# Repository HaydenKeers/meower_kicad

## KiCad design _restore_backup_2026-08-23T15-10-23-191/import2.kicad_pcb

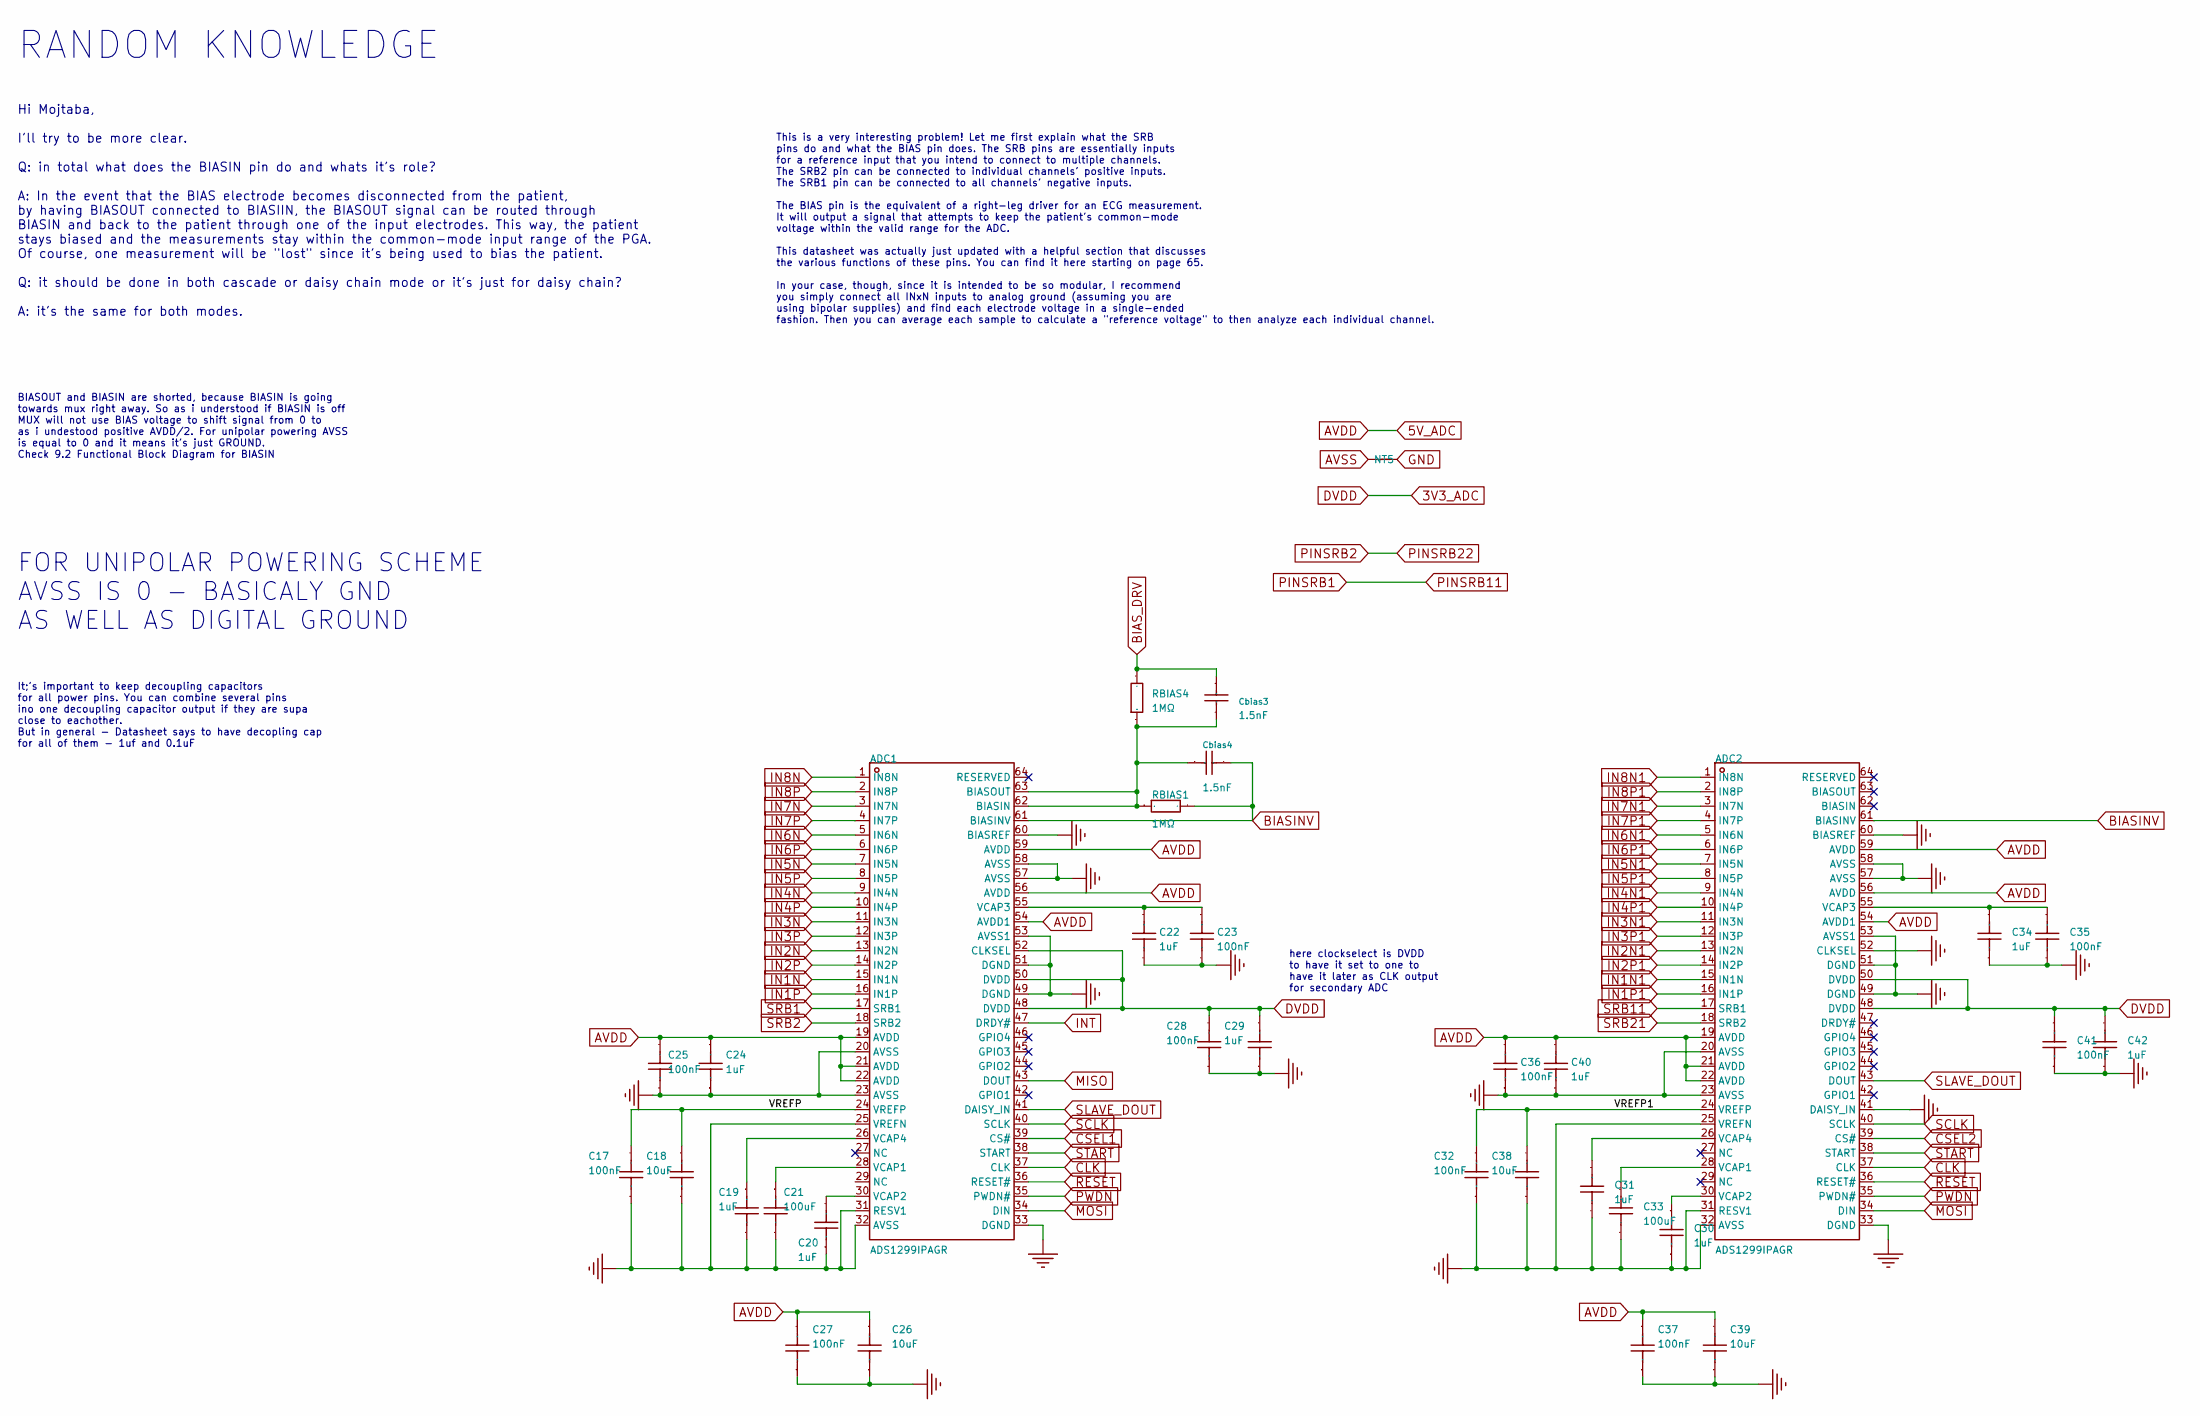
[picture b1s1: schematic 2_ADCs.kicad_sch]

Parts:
ADC1, ADC2: ADS1299IPAGR; TQFP-64_L10.0-W10.0-P0.50-LS12.0-TL; Voltage - Supply 4.75V~5.25V; Voltage Reference Drift 35ppm/℃; Manufacturer Part ADS1299IPAGR; LCSC Part Name ADS1299-x 低噪声、4/6/8通道、24bit 、同时采样模数转换器，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
C17, C23, C25, C27, C28, C32, C35, C36, C37, C41: 100nF; C0603; Manufacturer Part GRM188R71H104KA93D; LCSC Part Name 100nF ±10% 50V
C18, C26, C38, C39: 10uF; C0805; Manufacturer Part GRM188R61A106KE69D; LCSC Part Name 10uF ±10% 10V
C19, C20, C22, C30, C31, C34: 1uF; C0603; Manufacturer Part GRM188R61E105KA12D; LCSC Part Name 1uF ±10% 25V
C21, C33: 100uF; C1210; Manufacturer Part LMK325BJ107MM-T; LCSC Part Name 100uF ±20% 10V
C24, C29, C40, C42: 1uF; C0805; Manufacturer Part GRM188R61E105KA12D; LCSC Part Name 1uF ±10% 25V
Cbias3, Cbias4: 1.5nF; C0402; Voltage Rating 50V; Manufacturer Part GCM155R71H152KA37D; LCSC Part Name 1.5nF ±10% 50V
NT5: NetTie_2; NetTie-2_SMD_Pad0.5mm
RBIAS1, RBIAS4: 1MΩ; R0603; Manufacturer Part RC0402FR-071ML; LCSC Part Name 厚膜电阻 1MΩ ±1% 62.5mW

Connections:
3V3_ADC: ADC1.48 (DVDD), ADC1.50 (DVDD), ADC1.52 (CLKSEL), ADC2.48 (DVDD), ADC2.50 (DVDD), C28.2, C29.2, C41.2, C42.2; also elsewhere on the board
5V_ADC: ADC1.19 (AVDD), ADC1.21 (AVDD), ADC1.22 (AVDD), ADC1.54 (AVDD1), ADC1.56 (AVDD), ADC1.59 (AVDD), ADC2.19 (AVDD), ADC2.21 (AVDD), ADC2.22 (AVDD), ADC2.54 (AVDD1), ADC2.56 (AVDD), ADC2.59 (AVDD), C24.2, C25.2, C26.2, C27.2, C36.2, C37.2, C39.2, C40.2; also elsewhere on the board
/ADCs/VREFP: ADC1.24 (VREFP), C17.2, C18.2
/ADCs/VREFP1: ADC2.24 (VREFP), C32.2, C38.2
AVSS: ADC1.20 (AVSS), ADC1.23 (AVSS), ADC1.25 (VREFN), ADC1.31 (RESV1), ADC1.32 (AVSS), ADC1.57 (AVSS), ADC1.58 (AVSS), ADC1.60 (BIASREF), ADC2.20 (AVSS), ADC2.23 (AVSS), ADC2.25 (VREFN), ADC2.31 (RESV1), ADC2.32 (AVSS), ADC2.57 (AVSS), ADC2.58 (AVSS), ADC2.60 (BIASREF), C17.1, C18.1, C19.2, C20.1, C21.2, C24.1, C25.1, C30.1, C31.2, C32.1, C33.2, C36.1, C38.1, C40.1, NT5.1; also elsewhere on the board
BIASINV: ADC1.61 (BIASINV), ADC2.61 (BIASINV), Cbias4.2, RBIAS1.2
BIAS_DRV: Cbias3.1, RBIAS4.2; also elsewhere on the board
CLK: ADC1.37 (CLK), ADC2.37 (CLK)
CSEL1: ADC1.39 (CS#); also elsewhere on the board
CSEL2: ADC2.39 (CS#); also elsewhere on the board
GND: ADC1.33 (DGND), ADC1.49 (DGND), ADC1.51 (DGND), ADC1.53 (AVSS1), ADC2.33 (DGND), ADC2.41 (DAISY_IN), ADC2.49 (DGND), ADC2.51 (DGND), ADC2.52 (CLKSEL), ADC2.53 (AVSS1), C22.2, C23.2, C26.1, C27.1, C28.1, C29.1, C34.2, C35.2, C37.1, C39.1, C41.1, C42.1, NT5.2; also elsewhere on the board
IN1N: ADC1.15 (IN1N); also elsewhere on the board
IN1N1: ADC2.15 (IN1N); also elsewhere on the board
IN1P: ADC1.16 (IN1P); also elsewhere on the board
IN1P1: ADC2.16 (IN1P); also elsewhere on the board
IN2N: ADC1.13 (IN2N); also elsewhere on the board
IN2N1: ADC2.13 (IN2N); also elsewhere on the board
IN2P: ADC1.14 (IN2P); also elsewhere on the board
IN2P1: ADC2.14 (IN2P); also elsewhere on the board
IN3N: ADC1.11 (IN3N); also elsewhere on the board
IN3N1: ADC2.11 (IN3N); also elsewhere on the board
IN3P: ADC1.12 (IN3P); also elsewhere on the board
IN3P1: ADC2.12 (IN3P); also elsewhere on the board
IN4N: ADC1.9 (IN4N); also elsewhere on the board
IN4N1: ADC2.9 (IN4N); also elsewhere on the board
IN4P: ADC1.10 (IN4P); also elsewhere on the board
IN4P1: ADC2.10 (IN4P); also elsewhere on the board
IN5N: ADC1.7 (IN5N); also elsewhere on the board
IN5N1: ADC2.7 (IN5N); also elsewhere on the board
IN5P: ADC1.8 (IN5P); also elsewhere on the board
IN5P1: ADC2.8 (IN5P); also elsewhere on the board
IN6N: ADC1.5 (IN6N); also elsewhere on the board
IN6N1: ADC2.5 (IN6N); also elsewhere on the board
IN6P: ADC1.6 (IN6P); also elsewhere on the board
IN6P1: ADC2.6 (IN6P); also elsewhere on the board
IN7N: ADC1.3 (IN7N); also elsewhere on the board
IN7N1: ADC2.3 (IN7N); also elsewhere on the board
IN7P: ADC1.4 (IN7P); also elsewhere on the board
IN7P1: ADC2.4 (IN7P); also elsewhere on the board
IN8N: ADC1.1 (IN8N); also elsewhere on the board
IN8N1: ADC2.1 (IN8N); also elsewhere on the board
IN8P: ADC1.2 (IN8P); also elsewhere on the board
IN8P1: ADC2.2 (IN8P); also elsewhere on the board
INT: ADC1.47 (DRDY#); also elsewhere on the board
MISO: ADC1.43 (DOUT); also elsewhere on the board
MOSI: ADC1.34 (DIN), ADC2.34 (DIN); also elsewhere on the board
unnamed: ADC1.62 (BIASIN), ADC1.63 (BIASOUT), Cbias3.2, Cbias4.1, RBIAS1.1, RBIAS4.1
unnamed: ADC1.28 (VCAP1), C21.1
unnamed: ADC1.30 (VCAP2), C20.2
unnamed: ADC1.55 (VCAP3), C22.1, C23.1
unnamed: ADC1.26 (VCAP4), C19.1
unnamed: ADC2.28 (VCAP1), C33.1
unnamed: ADC2.30 (VCAP2), C30.2
unnamed: ADC2.55 (VCAP3), C34.1, C35.1
unnamed: ADC2.26 (VCAP4), C31.1
PWDN: ADC1.35 (PWDN#), ADC2.35 (PWDN#); also elsewhere on the board
RESET: ADC1.36 (RESET#), ADC2.36 (RESET#); also elsewhere on the board
SCLK: ADC1.40 (SCLK), ADC2.40 (SCLK); also elsewhere on the board
SLAVE_DOUT: ADC1.41 (DAISY_IN), ADC2.43 (DOUT)
SRB1: ADC1.17 (SRB1); also elsewhere on the board
SRB2: ADC1.18 (SRB2); also elsewhere on the board
SRB11: ADC2.17 (SRB1); also elsewhere on the board
SRB21: ADC2.18 (SRB2); also elsewhere on the board
START: ADC1.38 (START), ADC2.38 (START); also elsewhere on the board

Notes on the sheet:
It;'s important to keep decoupling capacitors for all power pins. You can combine several pins ino one decoupling capacitor output if they are supa close to eachother. But in general - Datasheet says to have decopling cap for all of them - 1uf and 0.1uF
FOR UNIPOLAR POWERING SCHEME AVSS IS 0 - BASICALY GND AS WELL AS DIGITAL GROUND
Hi Mojtaba, I'll try to be more clear. Q: in total what does the BIASIN pin do and whats it's role? A: In the event that the BIAS electrode becomes disconnected from the patient, by having BIASOUT connected to BIASIIN, the BIASOUT signal can be routed through BIASIN and back to the patient through 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
BIASOUT and BIASIN are shorted, because BIASIN is going towards mux right away. So as i understood if BIASIN is off MUX will not use BIAS voltage to shift signal from 0 to as i undestood positive AVDD/2. For unipolar powering AVSS is equal to 0 and it means it's just GROUND. Check 9.2 Functional Bl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
here clockselect is DVDD to have it set to one to have it later as CLK output for secondary ADC
This is a very interesting problem! Let me first explain what the SRB pins do and what the BIAS pin does. The SRB pins are essentially inputs for a reference input that you intend to connect to multiple channels. The SRB2 pin can be connected to individual channels' positive inputs. The SRB1 pin ca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
RANDOM KNOWLEDGE

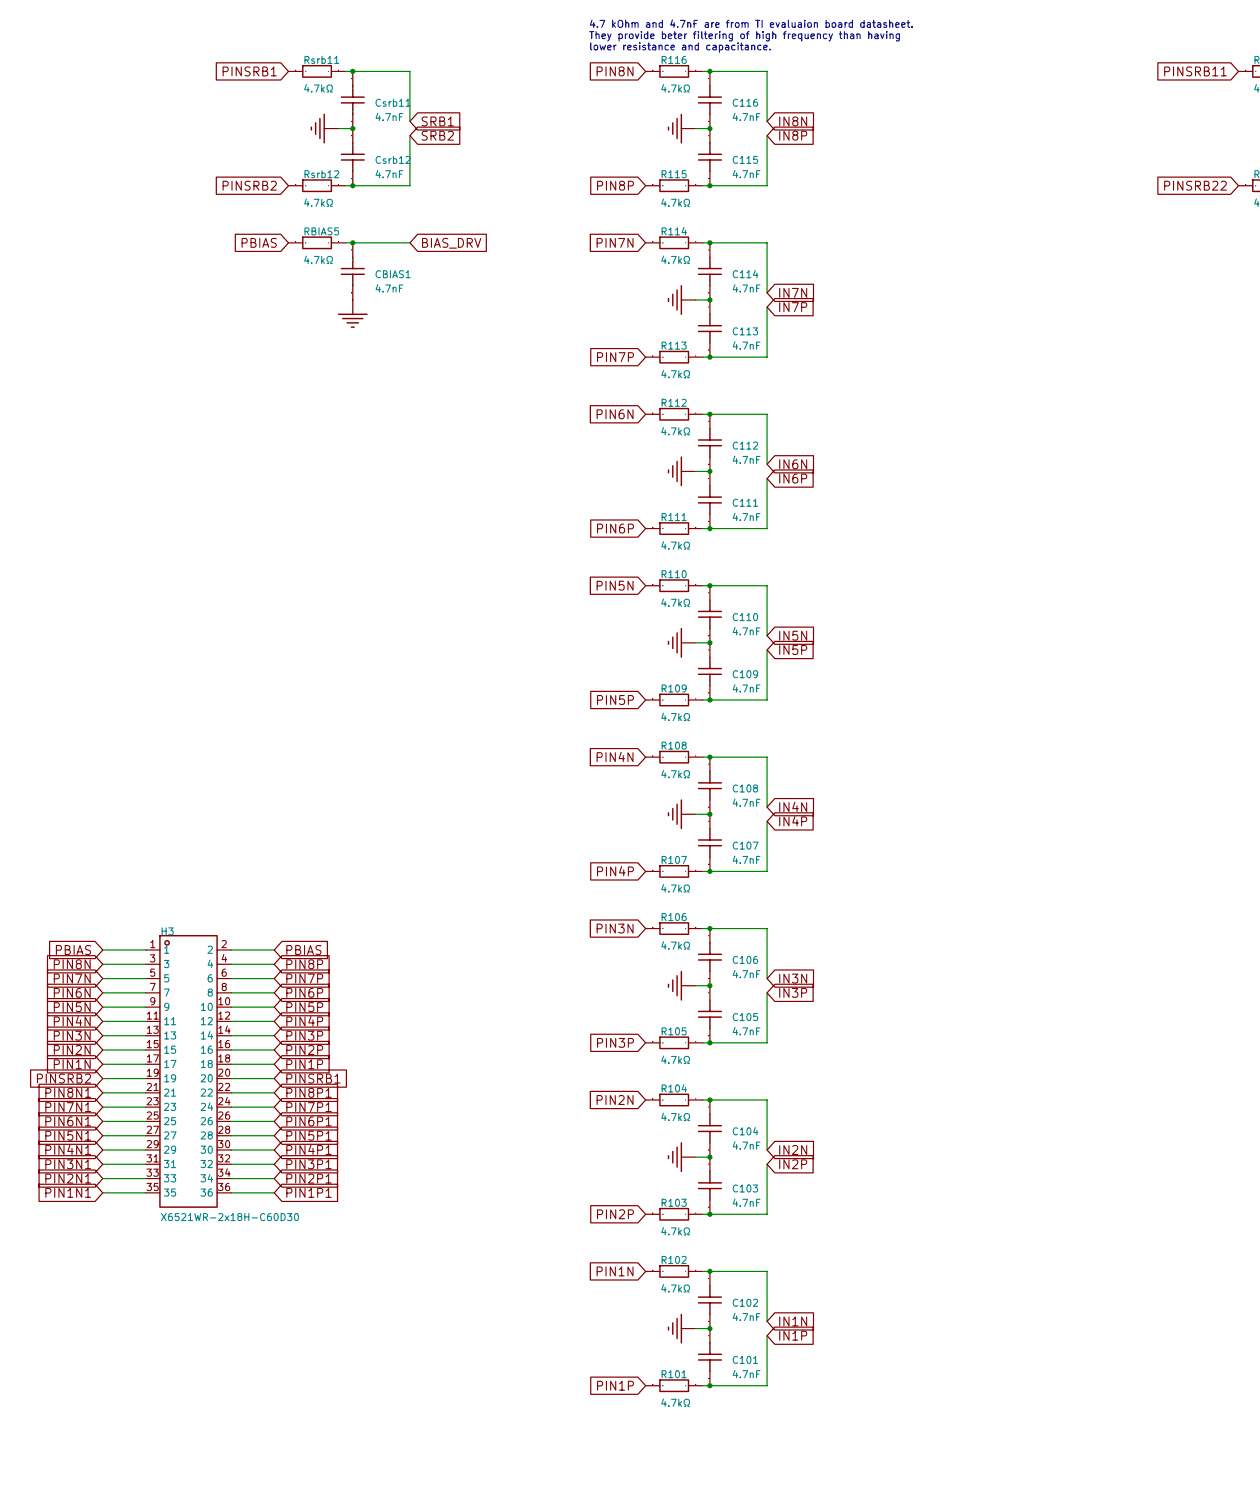
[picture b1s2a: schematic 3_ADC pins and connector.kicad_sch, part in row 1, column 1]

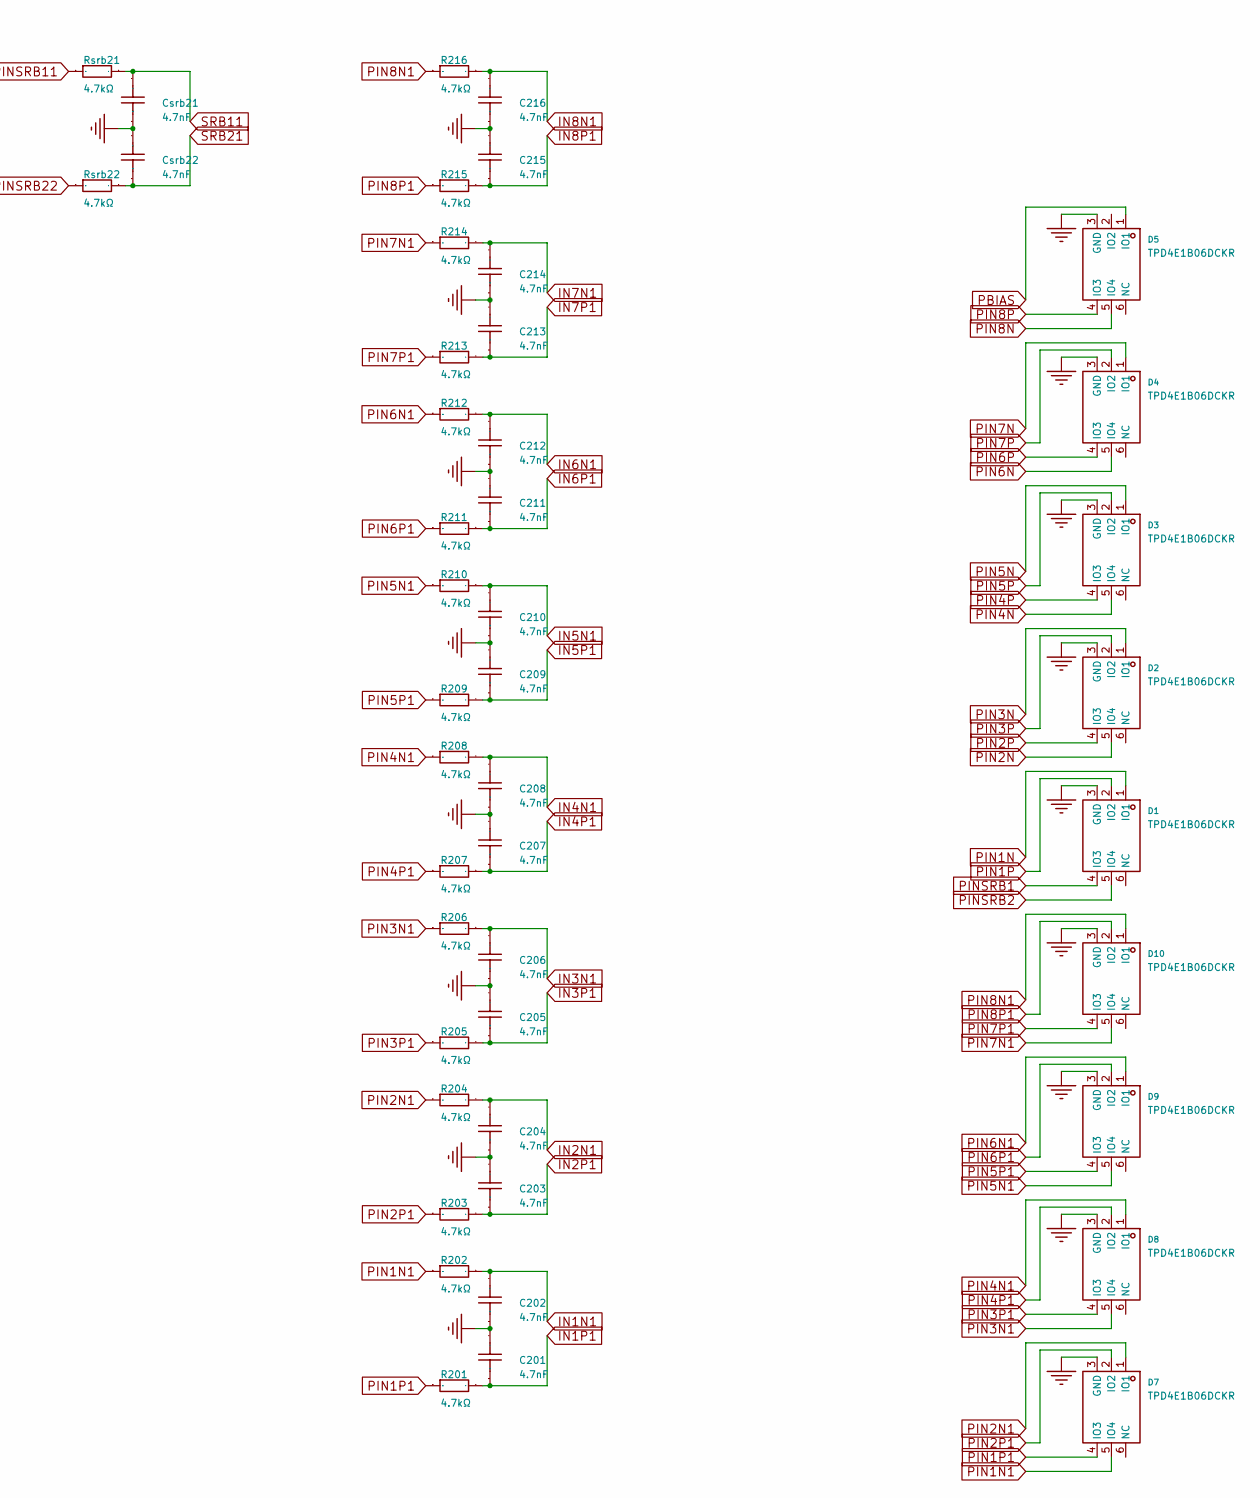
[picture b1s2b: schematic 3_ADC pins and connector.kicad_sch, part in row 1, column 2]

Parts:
C101, C102, C103, C104, C105, C106, C107, C108, C109, C110, C111, C112, C113, C114, C115, C116, C201, C202, C203, C204, C205, C206, C207, C208, C209, C210, C211, C212, C213, C214, C215, C216: 4.7nF; C0402; Tolerance ±2%; Voltage Rating 50V; Manufacturer Part GRM1555C1H472GE01D; LCSC Part Name 4.7nF ±2% 50V
CBIAS1: 4.7nF; C0402; Tolerance ±2%; Voltage Rating 50V; Manufacturer Part GRM1555C1H472GE01D; LCSC Part Name 4.7nF ±2% 50V
Csrb11, Csrb12, Csrb21, Csrb22: 4.7nF; C0402; Tolerance ±2%; Voltage Rating 50V; Manufacturer Part GRM1555C1H472GE01D; LCSC Part Name 4.7nF ±2% 50V
D1, D2, D3, D4, D5, D7, D8, D9, D10: TPD4E1B06DCKR; SC-70-6_L2.2-W1.3-P0.65-LS2.1-BL; Manufacturer Part TPD4E1B06DCKR; LCSC Part Name TPD4E1B06DCKR
H3: X6521WR-2x18H-C60D30; HDR-TH_36P-P2.54-H-M-R2-C18-S2.54; Manufacturer Part X6521WR-2x18H-C60D30; LCSC Part Name 2x18P 间距:2.54mm 方针
R101, R102, R103, R104, R105, R106, R107, R108, R109, R110, R111, R112, R113, R114, R115, R116, R201, R202, R203, R204, R205, R206, R207, R208, R209, R210, R211, R212, R213, R214, R215, R216: 4.7kΩ; R0402; Manufacturer Part RC0402FR-074K7L; LCSC Part Name 厚膜电阻 4.7kΩ ±1% 62.5mW
RBIAS5: 4.7kΩ; R0402; Manufacturer Part RC0402FR-074K7L; LCSC Part Name 厚膜电阻 4.7kΩ ±1% 62.5mW
Rsrb11, Rsrb12, Rsrb21, Rsrb22: 4.7kΩ; R0402; Manufacturer Part RC0402FR-074K7L; LCSC Part Name 厚膜电阻 4.7kΩ ±1% 62.5mW

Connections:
AVSS: C101.2, C102.1, C103.2, C104.1, C105.2, C106.1, C107.2, C108.1, C109.2, C110.1, C111.2, C112.1, C113.2, C114.1, C115.2, C116.1, C201.2, C202.1, C203.2, C204.1, C205.2, C206.1, C207.2, C208.1, C209.2, C210.1, C211.2, C212.1, C213.2, C214.1, C215.2, C216.1, CBIAS1.1, Csrb11.1, Csrb12.2, Csrb21.1, Csrb22.2, D1.3 (GND), D2.3 (GND), D3.3 (GND), D4.3 (GND), D5.3 (GND), D7.3 (GND), D8.3 (GND), D9.3 (GND), D10.3 (GND); also elsewhere on the board
BIAS_DRV: CBIAS1.2, RBIAS5.2; also elsewhere on the board
IN1N: C102.2, R102.2; also elsewhere on the board
IN1N1: C202.2, R202.2; also elsewhere on the board
IN1P: C101.1, R101.2; also elsewhere on the board
IN1P1: C201.1, R201.2; also elsewhere on the board
IN2N: C104.2, R104.2; also elsewhere on the board
IN2N1: C204.2, R204.2; also elsewhere on the board
IN2P: C103.1, R103.2; also elsewhere on the board
IN2P1: C203.1, R203.2; also elsewhere on the board
IN3N: C106.2, R106.2; also elsewhere on the board
IN3N1: C206.2, R206.2; also elsewhere on the board
IN3P: C105.1, R105.2; also elsewhere on the board
IN3P1: C205.1, R205.2; also elsewhere on the board
IN4N: C108.2, R108.2; also elsewhere on the board
IN4N1: C208.2, R208.2; also elsewhere on the board
IN4P: C107.1, R107.2; also elsewhere on the board
IN4P1: C207.1, R207.2; also elsewhere on the board
IN5N: C110.2, R110.2; also elsewhere on the board
IN5N1: C210.2, R210.2; also elsewhere on the board
IN5P: C109.1, R109.2; also elsewhere on the board
IN5P1: C209.1, R209.2; also elsewhere on the board
IN6N: C112.2, R112.2; also elsewhere on the board
IN6N1: C212.2, R212.2; also elsewhere on the board
IN6P: C111.1, R111.2; also elsewhere on the board
IN6P1: C211.1, R211.2; also elsewhere on the board
IN7N: C114.2, R114.2; also elsewhere on the board
IN7N1: C214.2, R214.2; also elsewhere on the board
IN7P: C113.1, R113.2; also elsewhere on the board
IN7P1: C213.1, R213.2; also elsewhere on the board
IN8N: C116.2, R116.2; also elsewhere on the board
IN8N1: C216.2, R216.2; also elsewhere on the board
IN8P: C115.1, R115.2; also elsewhere on the board
IN8P1: C215.1, R215.2; also elsewhere on the board
PBIAS: D5.1 (IO1), H3.1, H3.2, RBIAS5.1
PIN1N: D1.1 (IO1), H3.17, R102.1
PIN1N1: D7.5 (IO4), H3.35, R202.1
PIN1P: D1.2 (IO2), H3.18, R101.1
PIN1P1: D7.4 (IO3), H3.36, R201.1
PIN2N: D2.5 (IO4), H3.15, R104.1
PIN2N1: D7.1 (IO1), H3.33, R204.1
PIN2P: D2.4 (IO3), H3.16, R103.1
PIN2P1: D7.2 (IO2), H3.34, R203.1
PIN3N: D2.1 (IO1), H3.13, R106.1
PIN3N1: D8.5 (IO4), H3.31, R206.1
PIN3P: D2.2 (IO2), H3.14, R105.1
PIN3P1: D8.4 (IO3), H3.32, R205.1
PIN4N: D3.5 (IO4), H3.11, R108.1
PIN4N1: D8.1 (IO1), H3.29, R208.1
PIN4P: D3.4 (IO3), H3.12, R107.1
PIN4P1: D8.2 (IO2), H3.30, R207.1
PIN5N: D3.1 (IO1), H3.9, R110.1
PIN5N1: D9.5 (IO4), H3.27, R210.1
PIN5P: D3.2 (IO2), H3.10, R109.1
PIN5P1: D9.4 (IO3), H3.28, R209.1
PIN6N: D4.5 (IO4), H3.7, R112.1
PIN6N1: D9.1 (IO1), H3.25, R212.1
PIN6P: D4.4 (IO3), H3.8, R111.1
PIN6P1: D9.2 (IO2), H3.26, R211.1
PIN7N: D4.1 (IO1), H3.5, R114.1
PIN7N1: D10.5 (IO4), H3.23, R214.1
PIN7P: D4.2 (IO2), H3.6, R113.1
PIN7P1: D10.4 (IO3), H3.24, R213.1
PIN8N: D5.5 (IO4), H3.3, R116.1
PIN8N1: D10.1 (IO1), H3.21, R216.1
PIN8P: D5.4 (IO3), H3.4, R115.1
PIN8P1: D10.2 (IO2), H3.22, R215.1
SRB1: Csrb11.2, Rsrb11.2; also elsewhere on the board
SRB2: Csrb12.1, Rsrb12.2; also elsewhere on the board
SRB11: Csrb21.2, Rsrb21.2; also elsewhere on the board
SRB21: Csrb22.1, Rsrb22.2; also elsewhere on the board

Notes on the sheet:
4.7 kOhm and 4.7nF are from TI evaluaion board datasheet. They provide beter filtering of high frequency than having lower resistance and capacitance.

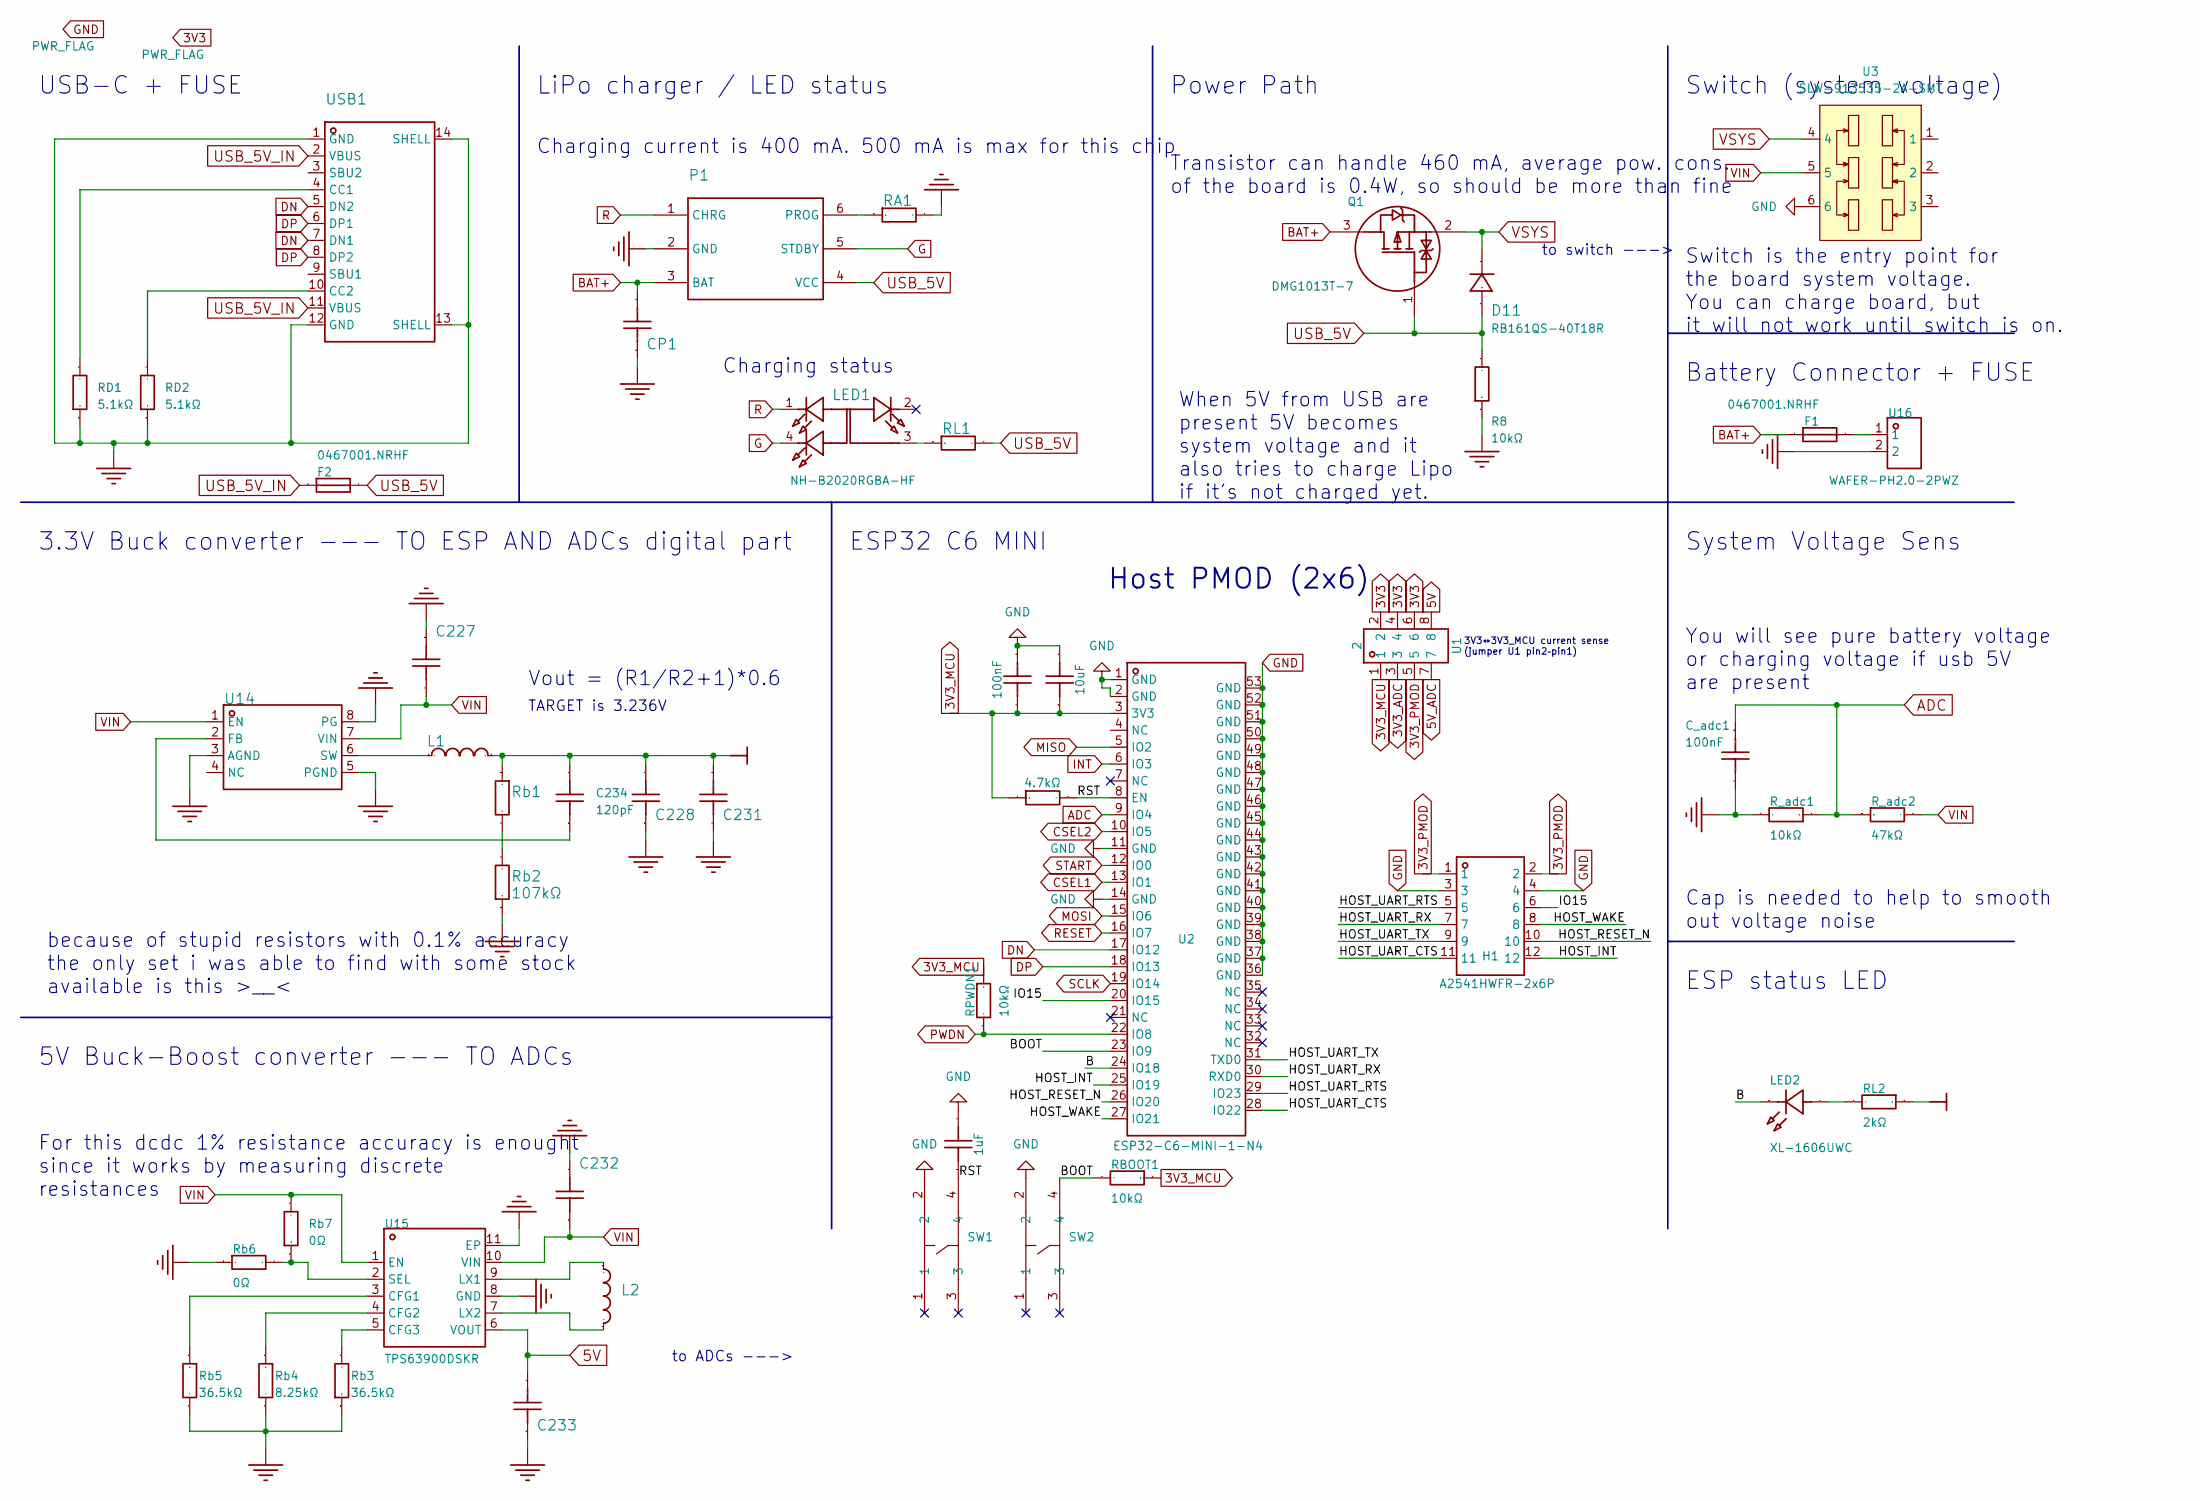
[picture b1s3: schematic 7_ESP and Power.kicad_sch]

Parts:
C222: 10uF; C0805; Manufacturer Part CL10A106KP8NNNC
C223: 100nF; C0603; Manufacturer Part GRM188R71H104KA93D
C224: 1uF; C0603; Manufacturer Part CL10A105KA8NNNC
C227: 4.7uF; C0603; Manufacturer Part GRM188Z71C475KE21D; LCSC Part Name 4.7uF ±10% 16V
C228, C231, C232: 10uF; C0603; Manufacturer Part GRM188Z71A106MA73D; LCSC Part Name 10uF ±20% 10V
C233: 22uF; C0603; Manufacturer Part GRM187R60J226ME15D; LCSC Part Name 22uF ±20% 6.3V
C234: 120pF; C0402; Tolerance ±1%; Voltage Rating 50V; Manufacturer Part AC0402FRNPO9BN121; LCSC Part Name 120pF ±1% 50V
CP1: 10uF; C0603; Manufacturer Part CL10A106KP8NNNC; LCSC Part Name 10uF ±10% 10V
C_adc1: 100nF; C0402; Voltage Rating 16V; Manufacturer Part CT41G-0402-2X1-16V-0.1uF-K(N); LCSC Part Name 100nF ±10% 16V
D11: RB161QS-40T18R; X2-DFN1006-2_L1.0-W0.6-P0.65-RD; Manufacturer Part RB161QS-40T18R; LCSC Part Name 电压:40V 电流:1A
F1, F2: 0467001.NRHF; F0603; Manufacturer Part 0467001.NRHF; LCSC Part Name 32V贴片式保险丝
H1: A2541HWFR-2x6P; HDR-TH_12P-P2.54-H-F-R2-C6-S2.54-W10.2; Manufacturer Part HC-PM254-8.5H-2x6PW
L1: 470nH; L1008; Manufacturer Part DFE201610E-R47M=P2; LCSC Part Name 470nH ±20% 4.8A
L2: 2.2uH; L1008; Manufacturer Part DFE252012F-2R2M=P2; LCSC Part Name 2.2uH ±20% 3.6A
LED1: NH-B2020RGBA-HF; LED-ARRAY-SMD_4P-L2.1-W2.1-TL_NH-B2020RGBA; Manufacturer Part NH-B2020RGBA-HF; LCSC Part Name NH-B2020RGBA-HF
LED2: XL-1606UWC; LED-SMD_L1.7-W0.6-RD; Manufacturer Part XL-1606UWC; LCSC Part Name XL-1606UWC
P1: SOT-23-6_L2.9-W1.6-P0.95-LS2.8-BL; Manufacturer Part TP4057-42-SOT26-R; LCSC Part Name TP4057 1%
Q1: DMG1013T-7; SC-75-3_L1.6-W0.8-P1.00-LS1.6-BR; Manufacturer Part DMG1013T-7; LCSC Part Name 1个P沟道 耐压:20V 电流:460mA
R1: 4.7kΩ; R0402; Manufacturer Part RC0402FR-074K7L
R8: 10kΩ; R0402; Overload Voltage (Max) 50V; Manufacturer Part 0402WGF1002TCE; LCSC Part Name 10kΩ ±1% 62.5mW 厚膜电阻
RA1: 2kΩ; R0402; Overload Voltage (Max) 50V; Manufacturer Part 0402WGF2001TCE; LCSC Part Name 2kΩ ±1% 62.5mW 厚膜电阻
RBOOT1: 10kΩ; R0402; Overload Voltage (Max) 50V; Manufacturer Part 0402WGJ0103TCE; LCSC Part Name 10kΩ ±1% 62.5mW 厚膜电阻
RD1, RD2: 5.1kΩ; R0402; Overload Voltage (Max) 50V; Manufacturer Part 0402WGF5101TCE; LCSC Part Name 5.1kΩ ±1% 62.5mW 厚膜电阻
RL1, RL2: 2kΩ; R0402; Overload Voltage (Max) 50V; Manufacturer Part 0402WGF2001TCE; LCSC Part Name 2kΩ ±1% 62.5mW 厚膜电阻
RPWDN1: 10kΩ; R0402; Overload Voltage (Max) 50V; Manufacturer Part 0402WGJ0103TCE; LCSC Part Name 10kΩ ±1% 62.5mW 厚膜电阻
R_adc1: 10kΩ; R0402; Overload Voltage (Max) 50V; Manufacturer Part 0402WGF1002TCE; LCSC Part Name 10kΩ ±1% 62.5mW 厚膜电阻
R_adc2: 47kΩ; R0402; Overload Voltage (Max) 50V; Manufacturer Part 0402WGF4702TCE; LCSC Part Name 47kΩ ±1% 62.5mW 厚膜电阻
Rb1: 470kΩ; R0402; Manufacturer Part AR02BTC4703; LCSC Part Name 薄膜电阻 470kΩ ±0.1% 62.5mW
Rb2: 107kΩ; R0402; Tolerance ±1%; Voltage-Supply(Max) 50V; Manufacturer Part RMC0402107K1%N; LCSC Part Name 107kΩ ±1% 62.5mW
Rb3, Rb5: 36.5kΩ; R0402; Manufacturer Part RC0402FR-0736K5L; LCSC Part Name 厚膜电阻 36.5kΩ ±1% 62.5mW
Rb4: 8.25kΩ; R0402; Manufacturer Part RC0402FR-078K25L; LCSC Part Name 厚膜电阻 8.25kΩ ±1% 62.5mW
Rb6: 0Ω; R0402; Manufacturer Part 0402WGF0000TCE; LCSC Part Name 0Ω ±1% 62.5mW 厚膜电阻
Rb7: 0Ω; R0402; Manufacturer Part RC0402FR-070RL; LCSC Part Name 厚膜电阻 0Ω ±1% 62.5mW
SW1, SW2: PTS810SJM250SMTRLFS; KEY-SMD_4P-L4.2-W3.2-P2.20-LS4.6; MPN PTS810SJM250SMTRLFS; LCSC Part C116501
U1: 2; HDR-TH_8P-P2.54-V-M-R2-C4-S2.54; Manufacturer Part 2541WV-2x04P
U2: ESP32-C6-MINI-1-N4; WIFIM-SMD_61P-L16.6-W13.2-P0.80-ESP32-C6-MINI-1-N4; Manufacturer Part ESP32-C6-MINI-1-N4
U3: SLW-913535-2A-SMT; SW-SMD_SLW-913535-2A-SMT; MPN SLW-913535-2A-SMT; LCSC Part C19626182
U14: VSON-8_L2.0-W1.5-P0.50-BL; Manufacturer Part TPS62821DLCR; LCSC Part Name TPS62821DLCR
U15: TPS63900DSKR; WSON-10_L2.5-W2.5-W0.50-TL-EP; Manufacturer Part TPS63900DSKR; LCSC Part Name 1.8V至5.5V,75nA超低静态电流同步升降压转换器
U16: WAFER-PH2.0-2PWZ; CONN-TH_2P-P2.00_GP01-2001WR-2P; Manufacturer Part WAFER-PH2.0-2PWZ; LCSC Part Name 1x2P 间距:2mm 弯插 系列:PH
USB1: USB-C-SMD_TYPE-C-6PIN-2MD-073; Manufacturer Part TYPE-C 16PIN 2MD(073); LCSC Part Name Type-C 母 卧贴

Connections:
3V3: C228.2, C231.1, C234.2, L1.2, RL2.1, Rb1.1, U1.2, U1.4, U1.6
3V3_ADC: U1.3; also elsewhere on the board
3V3_MCU: C222.1, C223.2, R1.1, RBOOT1.1, RPWDN1.1, U1.1, U2.3 (3V3)
3V3_PMOD: H1.1, H1.2, U1.5
5V: C233.2, U1.8, U15.6 (VOUT)
5V_ADC: U1.7; also elsewhere on the board
/ESP and Power/B: LED2.1 (K), U2.24 (IO18)
/ESP and Power/BOOT: RBOOT1.2, SW2.4, U2.23 (IO9)
/ESP and Power/HOST_INT: H1.12, U2.25 (IO19)
/ESP and Power/HOST_RESET_N: H1.10, U2.26 (IO20)
/ESP and Power/HOST_UART_CTS: H1.11, U2.28 (IO22)
/ESP and Power/HOST_UART_RTS: H1.5, U2.29 (IO23)
/ESP and Power/HOST_UART_RX: H1.7, U2.30 (RXD0)
/ESP and Power/HOST_UART_TX: H1.9, U2.31 (TXD0)
/ESP and Power/HOST_WAKE: H1.8, U2.27 (IO21)
/ESP and Power/IO15: H1.6, U2.20 (IO15)
/ESP and Power/RST: C224.1, R1.2, SW1.4, U2.8 (EN)
ADC: C_adc1.1, R_adc1.1, R_adc2.1, U2.9 (IO4)
BAT+: CP1.2, F1.1, P1.3 (BAT), Q1.3 (D)
CSEL1: U2.13 (IO1); also elsewhere on the board
CSEL2: U2.10 (IO5); also elsewhere on the board
DN: U2.17 (IO12), USB1.5 (DN2), USB1.7 (DN1)
DP: U2.18 (IO13), USB1.6 (DP1), USB1.8 (DP2)
G: LED1.4 (-), P1.5 (STDBY)
GND: C222.2, C223.1, C224.2, C227.1, C228.1, C231.2, C232.2, C233.1, CP1.1, C_adc1.2, H1.3, H1.4, P1.2 (GND), R8.1, RA1.2, RD1.1, RD2.1, R_adc1.2, Rb2.1, Rb3.1, Rb4.2, Rb5.2, Rb6.1, SW1.2, SW2.2, U2.1 (GND), U2.2 (GND), U2.11 (GND), U2.14 (GND), U2.36 (GND), U2.37 (GND), U2.38 (GND), U2.39 (GND), U2.40 (GND), U2.41 (GND), U2.42 (GND), U2.43 (GND), U2.44 (GND), U2.45 (GND), U2.46 (GND), U2.47 (GND), U2.48 (GND), U2.49 (GND), U2.50 (GND), U2.51 (GND), U2.52 (GND), U2.53 (GND), U3.6, U14.3 (AGND), U14.5 (PGND), U14.8 (PG), U15.8 (GND), U15.11 (EP), U16.2, USB1.1 (GND), USB1.12 (GND), USB1.13 (SHELL), USB1.14 (SHELL); also elsewhere on the board
INT: U2.6 (IO3); also elsewhere on the board
MISO: U2.5 (IO2); also elsewhere on the board
MOSI: U2.15 (IO6); also elsewhere on the board
unnamed: F1.2, U16.1
unnamed: LED1.3 (+), RL1.1
unnamed: LED2.2 (A), RL2.2
unnamed: P1.6 (PROG), RA1.1
unnamed: Rb1.2, Rb2.2
unnamed: C234.1, U14.2 (FB)
unnamed: L1.1, U14.6 (SW)
unnamed: Rb5.1, U15.3 (CFG1)
unnamed: Rb4.1, U15.4 (CFG2)
unnamed: Rb3.2, U15.5 (CFG3)
unnamed: L2.1, U15.9 (LX1)
unnamed: L2.2, U15.7 (LX2)
unnamed: Rb6.2, Rb7.1, U15.2 (SEL)
unnamed: RD1.2, USB1.4 (CC1)
unnamed: RD2.2, USB1.10 (CC2)
PWDN: RPWDN1.2, U2.22 (IO8); also elsewhere on the board
R: LED1.1 (-), P1.1 (CHRG)
RESET: U2.16 (IO7); also elsewhere on the board
SCLK: U2.19 (IO14); also elsewhere on the board
START: U2.12 (IO0); also elsewhere on the board
USB_5V: D11.2 (A), F2.2, P1.4 (VCC), Q1.1 (G), R8.2, RL1.2
USB_5V_IN: F2.1, USB1.2 (VBUS), USB1.11 (VBUS)
VIN: C227.2, C232.1, R_adc2.2, Rb7.2, U3.5, U14.1 (EN), U14.7 (VIN), U15.1 (EN), U15.10 (VIN)
VSYS: D11.1 (C), Q1.2 (S), U3.4

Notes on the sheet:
5V Buck-Boost converter --- TO ADCs
You will see pure battery voltage or charging voltage if usb 5V are present
Charging current is 400 mA. 500 mA is max for this chip
ESP32 C6 MINI
Transistor can handle 460 mA, average pow. cons. of the board is 0.4W, so should be more than fine
LiPo charger / LED status
Vout = (R1/R2+1)*0.6
Switch is the entry point for the board system voltage. You can charge board, but it will not work until switch is on.
When 5V from USB are present 5V becomes system voltage and it also tries to charge Lipo if it's not charged yet.
USB-C + FUSE
For this dcdc 1% resistance accuracy is enought since it works by measuring discrete resistances
3V3↔3V3_MCU current sense (jumper U1 pin2–pin1)
Battery Connector + FUSE
3.3V Buck converter --- TO ESP AND ADCs digital part
ESP status LED
because of stupid resistors with 0.1% accuracy the only set i was able to find with some stock available is this >__<
to switch --->
System Voltage Sens
Switch (system voltage)
to ADCs --->
Host PMOD (2x6)
Charging status
Cap is needed to help to smooth out voltage noise
Power Path
TARGET is 3.236V

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
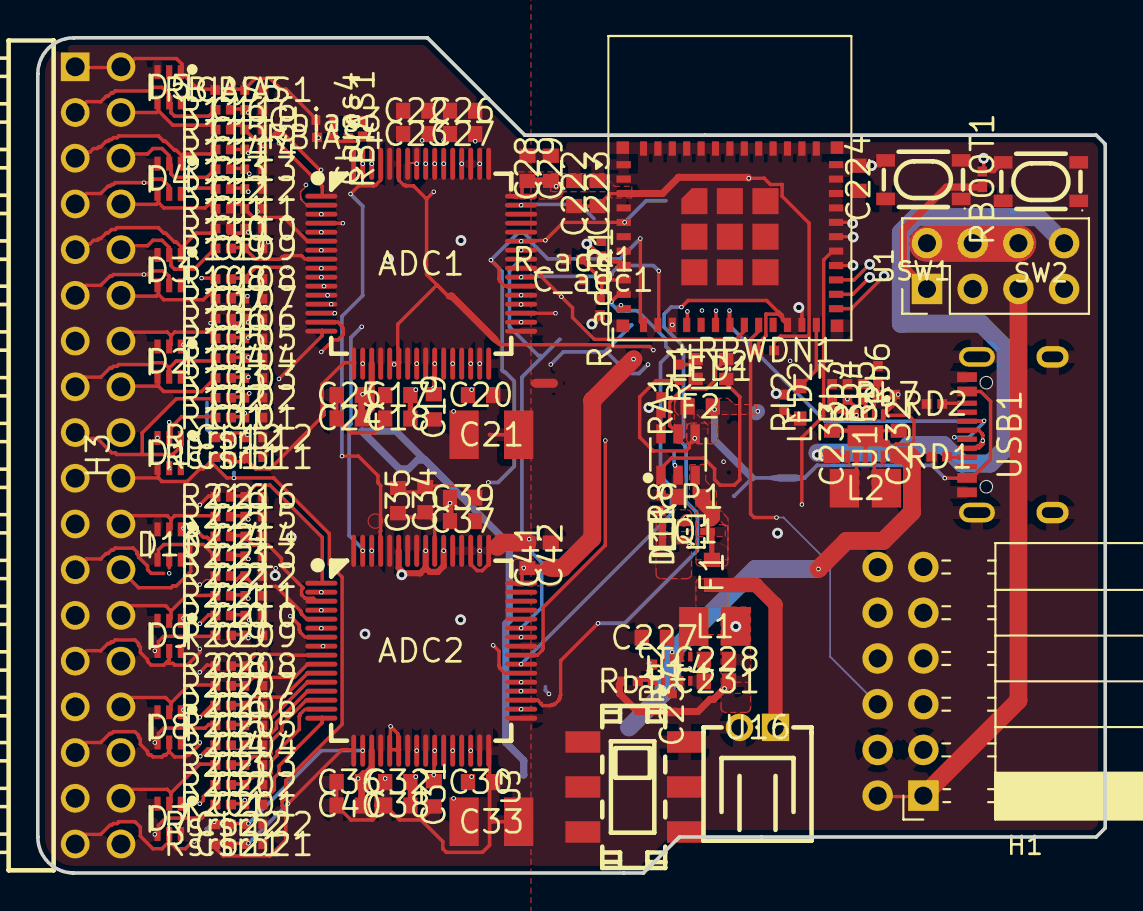
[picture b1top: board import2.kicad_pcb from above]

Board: 4 copper layers, 59.3 x 46.4 mm, 165 parts (0 on the bottom side), 139 nets.
